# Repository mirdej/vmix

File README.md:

# ANYMIX 21

Multichannel modular analog PAL video mixer based on the SYNKIE project

The Anymix21 is a 12 channel analog video mixer based on the paradigm of classic audio mixing desks.

Each channel is a complete SYNKIE by itself, sort of. It can handle anything from DC to around 10Mhz, this means you can mix CV signals with audio with PAL composite video signals. Contrary to an audio mixer, inputs are DC coupled, with 0v being black and 0.7V white level. Negative levels are permitted but will be clipped at the final output stage.

Each channel has a built-in equaliser, switchable edges (bandpass), comparator and inverter effects, and a scale-bias module for adjusting brightness and contrast. The signal can then be routed to 3 main output mix busses and an auxiliary output.

Apart from the equalizer, the effects and mix levels are digitally controlled analog, so parameters can be recorded, automated, or controlled externally through MIDI. The desk can be synchronized to a MIDI clock (which is then quantized to the vertical blanking interval derived from the genlock input).

Still under construction, the first 6 channels have passed their endurance test running daily for weeks at the exhibiton “H.o.Me. – Heim für obsolete Medien” at Kunsthaus Langenthal.

### Documentation
- Architecture [Overview](./doc/architecture.md)
- Mixer Channel: [Flowchart and description](./doc/channel.md)
- Master Section: [Flowchart and description](./doc/master.md)

### Links
- [Build pictures and notes](https://www.anyma.ch/blogs/research/2021/04/07/building-the-anymix21/) on my blog
- [https://www.anyma.ch](https://www.anyma.ch)
- [https://www.synkie.net](https://www.synkie.net)
- [Videos on Vimeo](https://vimeo.com/showcase/8252873)
- [Synkie on Github](https://github.com/mirdej/synkie)

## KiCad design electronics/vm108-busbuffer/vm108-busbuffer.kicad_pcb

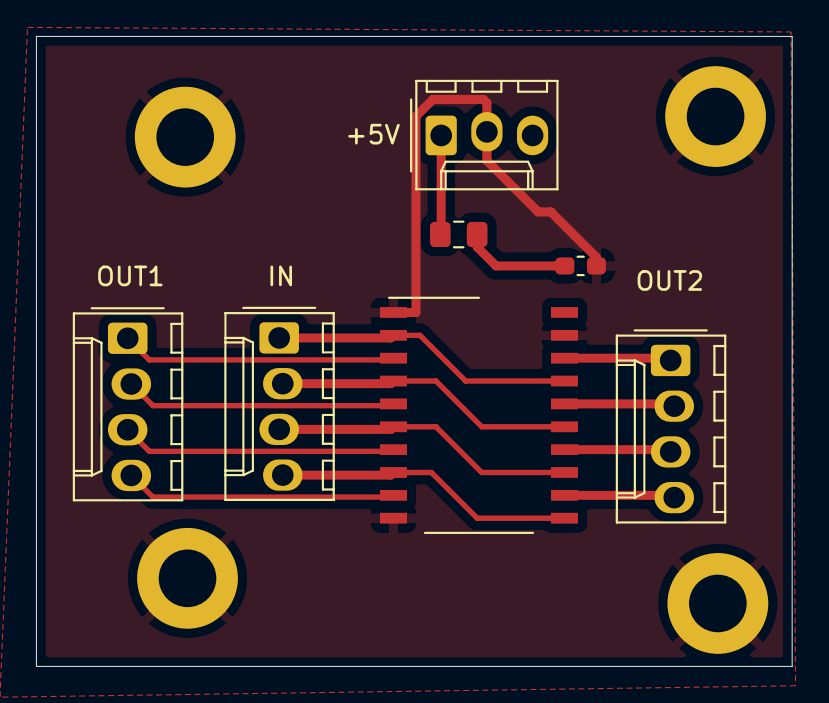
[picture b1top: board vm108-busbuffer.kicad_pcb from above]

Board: 2 copper layers, 42.0 x 35.0 mm, 11 parts (0 on the bottom side), 15 nets.

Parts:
C1: C; R_0603_1608Metric_Pad1.05x0.95mm_HandSolder
FB1: Ferrite_Bead; L_0805_2012Metric_Pad1.15x1.40mm_HandSolder
H1, H2, H3, H4: MountingHole_Pad; MountingHole_3.2mm_M3_DIN965_Pad
J1: Supply; Molex_KK-254_AE-6410-03A_1x03_P2.54mm_Vertical
J2, J3, J4: Sync-Bus; Molex_KK-254_AE-6410-04A_1x04_P2.54mm_Vertical
U1: 74HC244; SO-20_12.8x7.5mm_P1.27mm

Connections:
+5V: C1.1, FB1.2, U1.20 (VCC)
/supply+: FB1.1, J1.1
GND: C1.2, H1.1, H2.1, H3.1, H4.1, J1.2, U1.1 (1OE), U1.10 (GND), U1.19 (2OE)
unnamed: J2.1, U1.2 (1A0), U1.17 (2A0)
unnamed: J2.2, U1.4 (1A1), U1.15 (2A1)
unnamed: J2.3, U1.6 (1A2), U1.13 (2A2)
unnamed: J2.4, U1.8 (1A3), U1.11 (2A3)
unnamed: J3.1, U1.18 (1Y0)
unnamed: J3.2, U1.16 (1Y1)
unnamed: J3.3, U1.14 (1Y2)
unnamed: J3.4, U1.12 (1Y3)
unnamed: J4.1, U1.3 (2Y0)
unnamed: J4.2, U1.5 (2Y1)
unnamed: J4.3, U1.7 (2Y2)
unnamed: J4.4, U1.9 (2Y3)

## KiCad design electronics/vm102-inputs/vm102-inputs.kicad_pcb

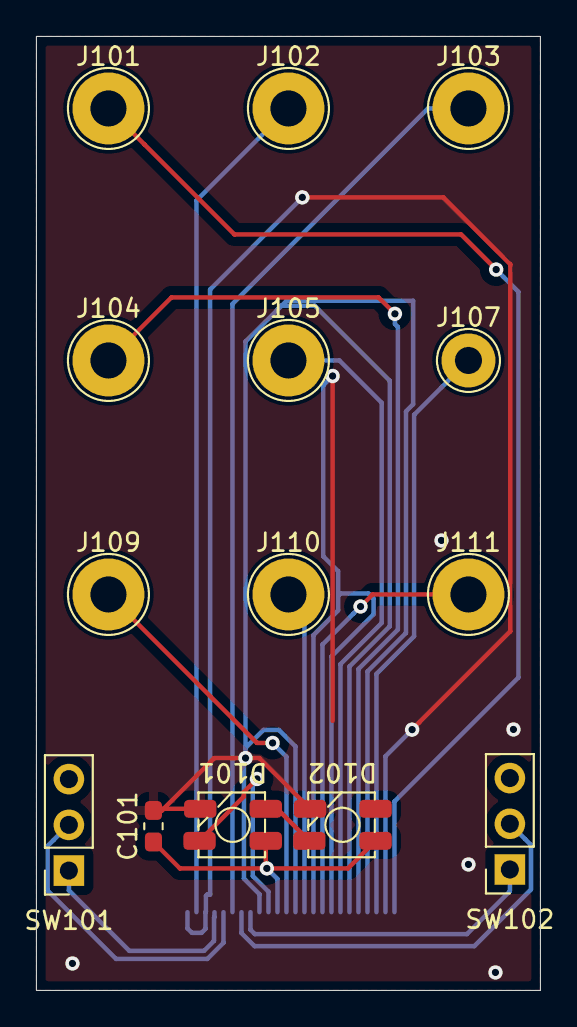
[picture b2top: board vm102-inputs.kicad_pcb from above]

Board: 2 copper layers, 28.0 x 53.0 mm, 15 parts (1 on the bottom side), 17 nets.

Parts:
C101: C; C_0603_1608Metric_Pad1.05x0.95mm_HandSolder
D101, D102: SK6812MINI; SK6812-MINI-HS
J101, J102, J103, J104, J105, J109, J110, J111: Conn; TestPoint_THTPad_D4.0mm_Drill2.0mm
J106: Conn_01x24_Shielded; Hirose_FH12-24S-0.5SH_1x24-1MP_P0.50mm_Horizontal
J107: Conn; TestPoint_THTPad_D3.0mm_Drill1.5mm
SW101, SW102: SW_SPDT; PinSocket_1x03_P2.54mm_Vertical

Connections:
/a: J106.12, J109.1
/aux: J105.1, J106.18
/b: J106.14, J110.1
/bias: J106.22, J107.1
/c: J106.16, J111.1
/compa-out: J102.1, J106.2
/hi_clip1: J106.8, SW102.1 (A)
/hi_clip2: J106.7, SW102.2 (B)
/lo_clip1: J106.4, SW101.1 (A)
/lo_clip2: J106.5, SW101.2 (B)
/output: J103.1, J106.6
/pixels: D101.3 (DIN), J106.10
/scale: J104.1, J106.20
/siff-in: J101.1, J106.24
GND: C101.2, D101.2 (VSS), D102.2 (VSS), J106.1, J106.3, J106.9, J106.13, J106.15, J106.17, J106.19, J106.21, J106.23
unnamed: D101.1 (DOUT), D102.3 (DIN)
VCC: C101.1, D101.4 (VDD), D102.4 (VDD), J106.11

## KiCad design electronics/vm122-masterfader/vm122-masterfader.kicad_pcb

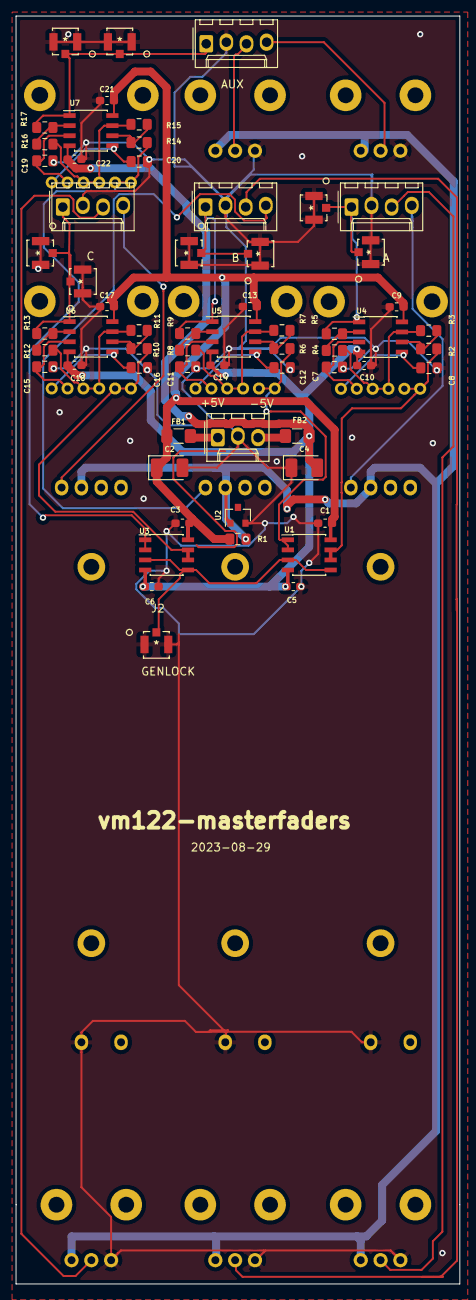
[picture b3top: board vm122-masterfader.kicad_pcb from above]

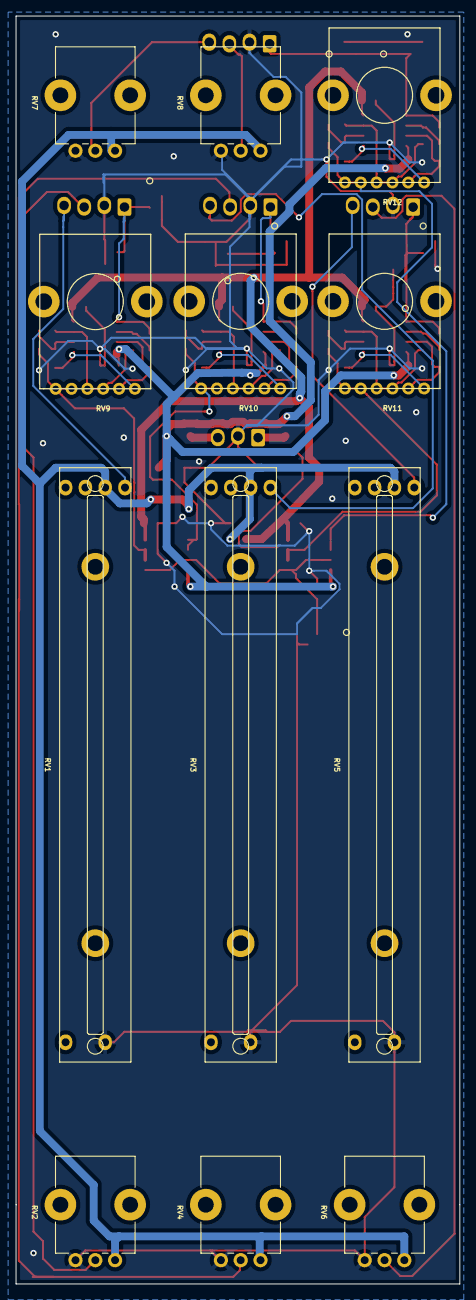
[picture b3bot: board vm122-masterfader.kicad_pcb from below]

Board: 2 copper layers, 56.0 x 160.0 mm, 74 parts (12 on the bottom side), 43 nets.

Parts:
C1, C3, C5, C6, C9, C10, C13, C14, C17, C18, C21, C22: 100n; C_0603_1608Metric_Pad1.05x0.95mm_HandSolder
C2, C4: CP; CP_EIA-3528-21_Kemet-B_Pad1.50x2.35mm_HandSolder
C7, C8, C11, C12, C15, C16, C19, C20: 10p; C_0805_2012Metric_Pad1.15x1.40mm_HandSolder
FB1, FB2: Ferrite_Bead; L_1206_3216Metric_Pad1.42x1.75mm_HandSolder
J1: Conn_01x03; Molex_KK-254_AE-6410-03A_1x03_P2.54mm_Vertical
J2, J7, J8, J9, J10, J11, J12, J13, J14: UMCC; TE_UMCC_2337019-1
J3: A; Molex_KK-254_AE-6410-04A_1x04_P2.54mm_Vertical
J4: B; Molex_KK-254_AE-6410-04A_1x04_P2.54mm_Vertical
J5: C; Molex_KK-254_AE-6410-04A_1x04_P2.54mm_Vertical
J6: D; Molex_KK-254_AE-6410-04A_1x04_P2.54mm_Vertical
R1: 560; R_0805_2012Metric_Pad1.15x1.40mm_HandSolder
R2, R3, R4, R5, R6, R7, R8, R9, R10, R11, R12, R13, R14, R15, R16, R17: 220; R_0805_2012Metric_Pad1.15x1.40mm_HandSolder
RV1, RV3, RV5: SCALE; Potentiometer_Alps_RS6011xP_Slide
RV2, RV4, RV6, RV8: BIAS; Potentiometer_Alps_RK09K_Single_Vertical
RV7: SCALE; Potentiometer_Alps_RK09K_Single_Vertical
RV9, RV10, RV11, RV12: R_POT_Dual; RK12L123
U1, U3, U4, U5, U6, U7: LMH6643; SOIC-8_3.9x4.9mm_P1.27mm
U2: ADR510; SOT-23

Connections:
+5V: C1.1, C2.1, C3.1, C9.2, C13.2, C17.2, C21.2, FB1.1, R1.1, U1.8 (V+), U3.8 (V+), U4.8 (V+), U5.8 (V+), U6.8 (V+), U7.8 (V+)
-5V: C4.2, C5.1, C6.1, C10.1, C14.1, C18.1, C22.1, FB2.1, U1.4 (V-), U3.4 (V-), U4.4 (V-), U5.4 (V-), U6.4 (V-), U7.4 (V-)
/Phase1/INPUT: R2.2, RV9.1, RV9.2, U1.6 (-), U1.7
/Phase1/OUTPUT: J3.1, J7.1, J8.1, R5.1, U4.1
/sheet5FF0F8E5/INPUT: R10.2, RV11.1, RV11.2, U3.6 (-), U3.7
/sheet5FF0F8E5/OUTPUT: J5.1, J11.1, J12.1, R13.1, U6.1
/sheet5FF0F40B/INPUT: R6.2, RV10.1, RV10.2, U1.1, U1.2 (-)
/sheet5FF0F40B/OUTPUT: J4.1, J9.1, J10.1, R9.1, U5.1
/sheet5FF0F904/INPUT: R14.2, RV12.1, RV12.2, U3.1, U3.2 (-)
/sheet5FF0F904/OUTPUT: J6.1, J13.1, J14.1, R17.1, U7.1
GND: C1.2, C2.2, C3.2, C4.1, C5.2, C6.2, C7.2, C8.2, C9.1, C10.2, C11.2, C12.2, C13.1, C14.2, C15.2, C16.2, C17.1, C18.2, C19.2, C20.2, C21.1, C22.2, J1.2, J2.2, J2.3, J3.2, J4.2, J5.2, J6.2, J7.2, J7.3, J8.2, J8.3, J9.2, J9.3, J10.2, J10.3, J11.2, J11.3, J12.2, J12.3, J13.2, J13.3, J14.2, J14.3, RV1.3, RV2.3, RV3.3, RV4.3, RV5.3, RV6.3, RV7.3, RV8.3, U2.2 (V-)
unnamed: C7.1, RV9.6, U4.3 (+)
unnamed: C8.1, RV9.3, U4.5 (+)
unnamed: C11.1, RV10.6, U5.3 (+)
unnamed: C12.1, RV10.3, U5.5 (+)
unnamed: C15.1, RV11.6, U6.3 (+)
unnamed: C16.1, RV11.3, U6.5 (+)
unnamed: C19.1, RV12.6, U7.3 (+)
unnamed: C20.1, RV12.3, U7.5 (+)
unnamed: FB1.2, J1.1
unnamed: FB2.2, J1.3
unnamed: J3.3, RV2.2
unnamed: J3.4, RV1.2
unnamed: J4.3, RV4.2
unnamed: J4.4, RV3.2
unnamed: J5.3, RV6.2
unnamed: J5.4, RV5.2
unnamed: J6.3, RV8.2
unnamed: J6.4, RV7.2
unnamed: R2.1, R3.2, U4.6 (-)
unnamed: R3.1, R4.2, RV9.4, RV9.5, U4.7
unnamed: R4.1, R5.2, U4.2 (-)
unnamed: R6.1, R7.2, U5.6 (-)
unnamed: R7.1, R8.2, RV10.4, RV10.5, U5.7
unnamed: R8.1, R9.2, U5.2 (-)
unnamed: R10.1, R11.2, U6.6 (-)
unnamed: R11.1, R12.2, RV11.4, RV11.5, U6.7
unnamed: R12.1, R13.2, U6.2 (-)
unnamed: R14.1, R15.2, U7.6 (-)
unnamed: R15.1, R16.2, RV12.4, RV12.5, U7.7
unnamed: R16.1, R17.2, U7.2 (-)
unnamed: J2.1, U1.3 (+), U1.5 (+), U3.3 (+), U3.5 (+)
VCCQ: R1.2, RV1.1, RV2.1, RV3.1, RV4.1, RV5.1, RV6.1, RV7.1, RV8.1, U2.1 (V+)

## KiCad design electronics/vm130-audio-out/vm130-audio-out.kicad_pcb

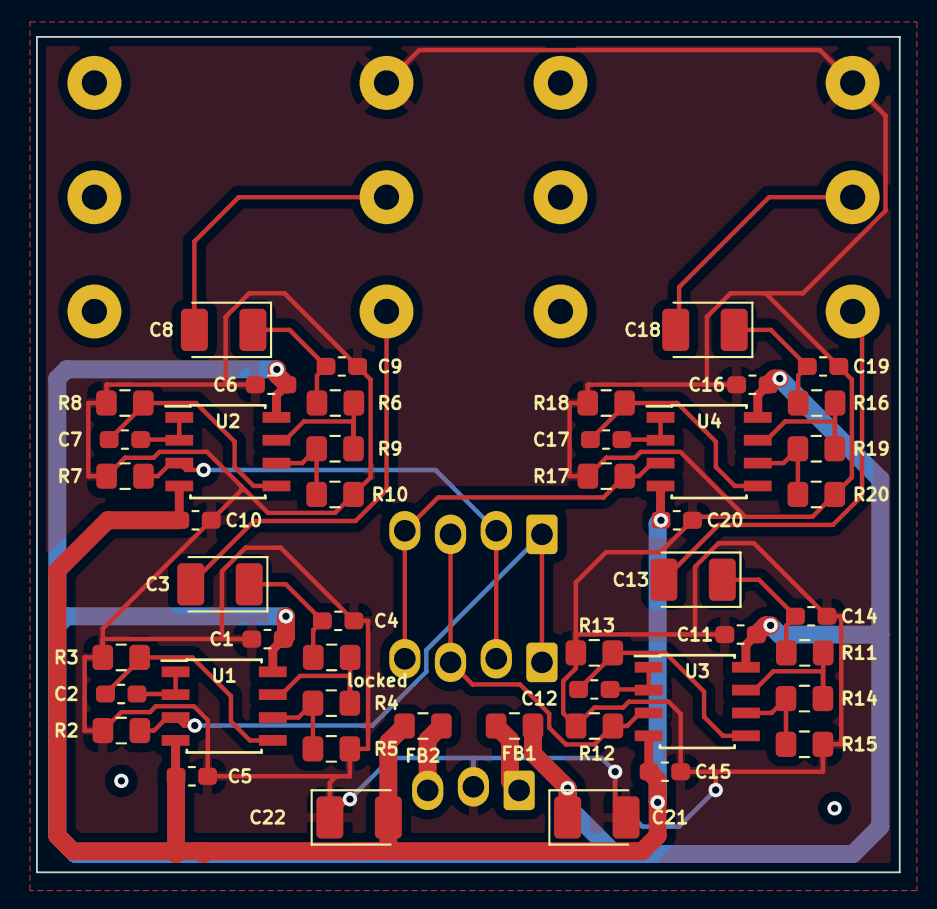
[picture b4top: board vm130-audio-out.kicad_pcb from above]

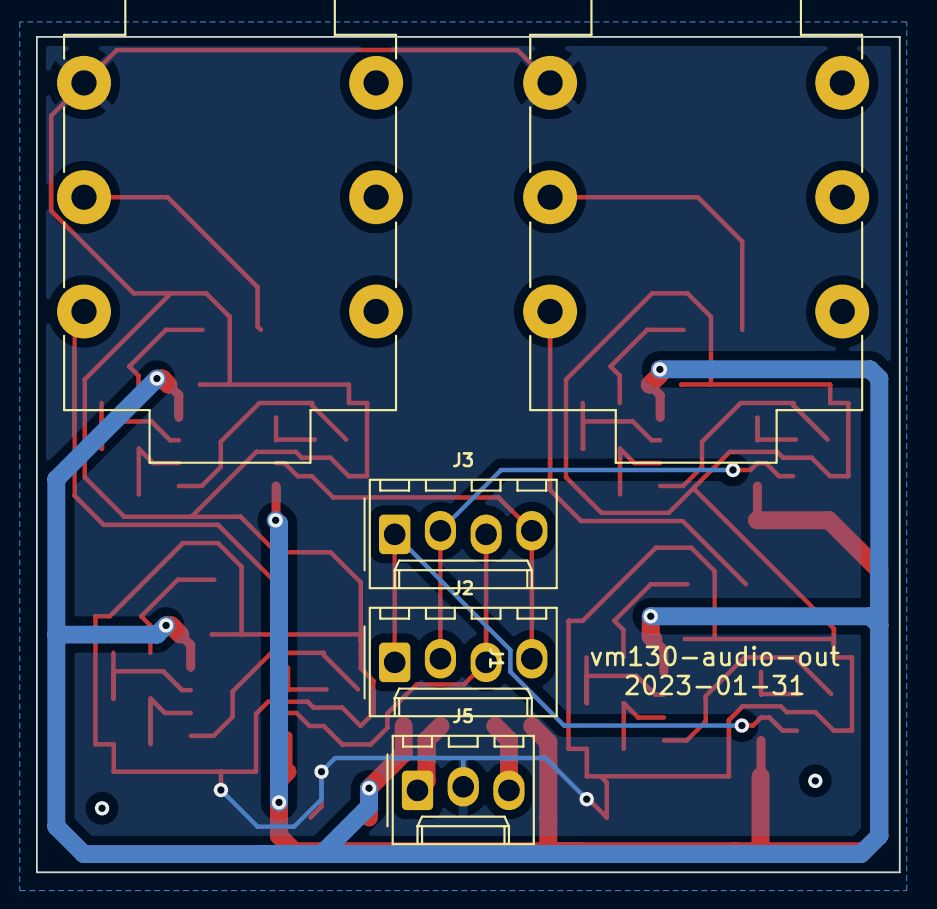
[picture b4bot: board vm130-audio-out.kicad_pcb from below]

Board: 2 copper layers, 47.9 x 46.4 mm, 53 parts (5 on the bottom side), 33 nets.

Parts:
C1, C4, C5, C6, C9, C10, C11, C14, C15, C16, C19, C20: 100n; C_0603_1608Metric_Pad1.05x0.95mm_HandSolder
C2, C7, C12, C17: 1u; C_0603_1608Metric_Pad1.05x0.95mm_HandSolder
C3, C8, C13, C18: 100u; CP_EIA-3528-21_Kemet-B_Pad1.50x2.35mm_HandSolder
C21, C22: CP; CP_EIA-3528-21_Kemet-B_Pad1.50x2.35mm_HandSolder
FB1, FB2: FerriteBead; L_0805_2012Metric_Pad1.15x1.40mm_HandSolder
J1, J4: AudioJack3_Switch; Jack_6.35mm_Neutrik_NMJ6HCD3_Horizontal
J2, J3: Conn_01x04; Molex_KK-254_AE-6410-04A_1x04_P2.54mm_Vertical
J5: Conn_01x03; Molex_KK-254_AE-6410-03A_1x03_P2.54mm_Vertical
R2, R7, R12, R17: 47k; C_0805_2012Metric_Pad1.15x1.40mm_HandSolder
R3, R8, R13, R18: 10k; C_0805_2012Metric_Pad1.15x1.40mm_HandSolder
R4, R5, R9, R10, R14, R15, R19, R20: 500; C_0805_2012Metric_Pad1.15x1.40mm_HandSolder
R6, R11, R16: 75; C_0805_2012Metric_Pad1.15x1.40mm_HandSolder
U1, U2, U3, U4: Opamp_Dual_Generic; SOIC-8_3.9x4.9mm_P1.27mm
locked: 75; C_0805_2012Metric_Pad1.15x1.40mm_HandSolder

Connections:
+5V: C1.2, C6.2, C11.2, C16.2, C21.1, FB1.2, U1.8 (V+), U2.8 (V+), U3.8 (V+), U4.8 (V+)
-5V: C5.2, C10.2, C15.2, C20.2, C22.2, FB2.2, U1.4 (V-), U2.4 (V-), U3.4 (V-), U4.4 (V-)
/channel1/out: C8.2, J1.R
/channel2/out: C13.2, J4.T
/channel3/out: C18.2, J4.R
/channel/out: C3.2, J1.T
/in-a: J2.1, J3.1, R2.1, U1.3 (+)
/in-b: J2.2, J3.2, R7.1, U2.3 (+)
/in-c: J2.3, J3.3, R12.1, U3.3 (+)
/in-d: J2.4, J3.4, R17.1, U4.3 (+)
GND: C1.1, C4.1, C5.1, C6.1, C9.1, C10.1, C11.1, C14.1, C15.1, C16.1, C19.1, C20.1, C21.2, C22.1, J1.S, J4.S, J5.2, R2.2, R3.2, R5.2, R7.2, R8.2, R10.2, R12.2, R13.2, R15.2, R17.2, R18.2, R20.2
unnamed: C2.1, U1.1, U1.2 (-)
unnamed: C2.2, R3.1, U1.5 (+)
unnamed: C3.1, C4.2, locked.2
unnamed: C7.1, U2.1, U2.2 (-)
unnamed: C7.2, R8.1, U2.5 (+)
unnamed: C8.1, C9.2, R6.2
unnamed: C12.1, U3.1, U3.2 (-)
unnamed: C12.2, R13.1, U3.5 (+)
unnamed: C13.1, C14.2, R11.2
unnamed: C17.1, U4.1, U4.2 (-)
unnamed: C17.2, R18.1, U4.5 (+)
unnamed: C18.1, C19.2, R16.2
unnamed: FB1.1, J5.1
unnamed: FB2.1, J5.3
unnamed: R4.2, U1.7, locked.1
unnamed: R4.1, R5.1, U1.6 (-)
unnamed: R6.1, R9.2, U2.7
unnamed: R9.1, R10.1, U2.6 (-)
unnamed: R11.1, R14.2, U3.7
unnamed: R14.1, R15.1, U3.6 (-)
unnamed: R16.1, R19.2, U4.7
unnamed: R19.1, R20.1, U4.6 (-)

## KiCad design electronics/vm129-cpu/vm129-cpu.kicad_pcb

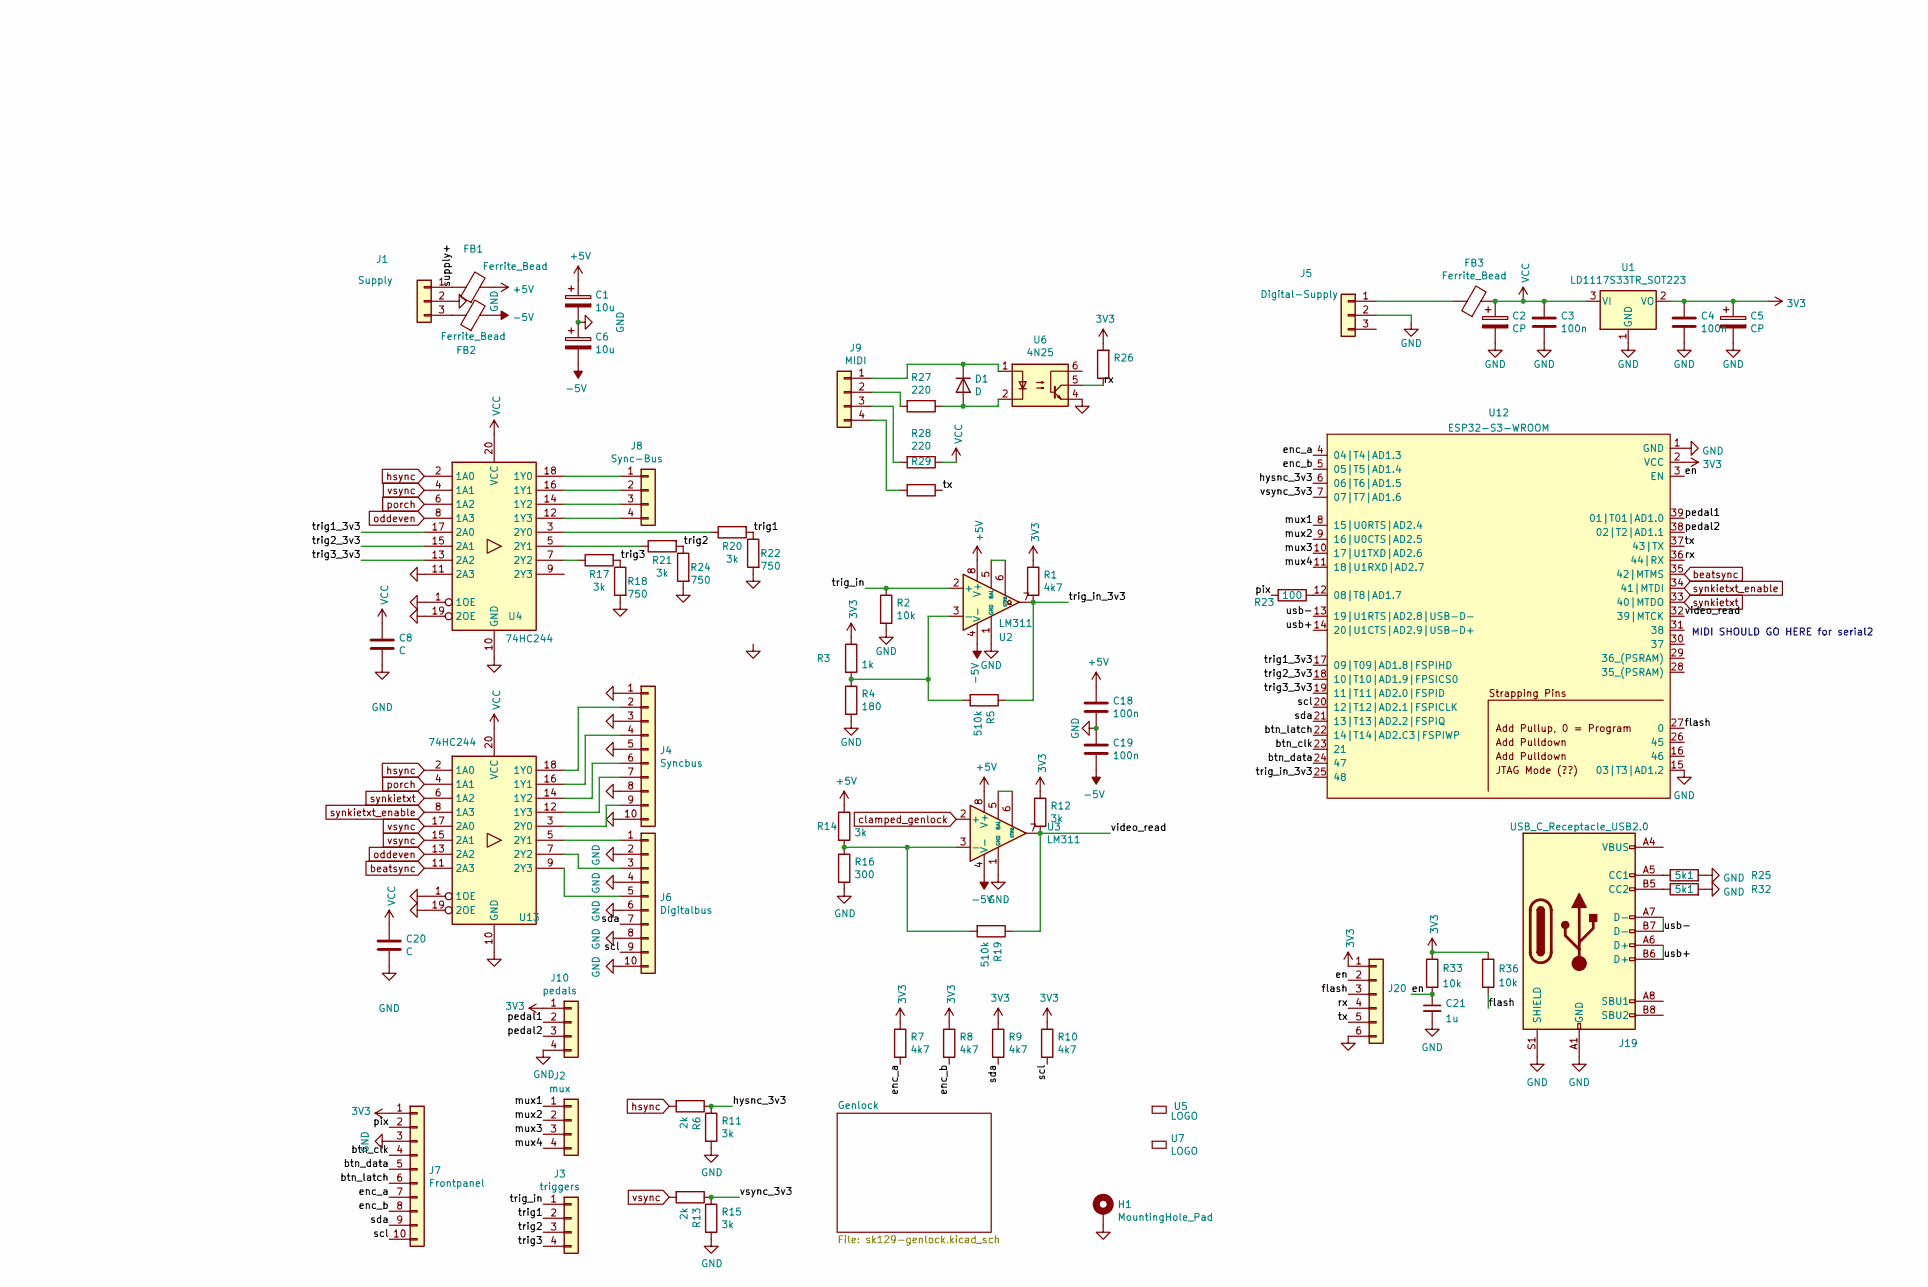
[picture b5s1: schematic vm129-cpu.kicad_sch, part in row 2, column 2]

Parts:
C1, C6: 10u; CP_EIA-3528-21_Kemet-B_Pad1.50x2.35mm_HandSolder
C2, C5: CP; CP_EIA-3528-21_Kemet-B_Pad1.50x2.35mm_HandSolder
C3, C4, C18, C19: 100n; C_0603_1608Metric_Pad1.05x0.95mm_HandSolder
C8, C20: C; R_0603_1608Metric_Pad1.05x0.95mm_HandSolder
C21: 1u; C_0603_1608Metric_Pad1.05x0.95mm_HandSolder
D1: D; D_MiniMELF
FB1, FB2, FB3: Ferrite_Bead; L_0805_2012Metric_Pad1.15x1.40mm_HandSolder
H1: MountingHole_Pad; MountingHole_2.7mm_M2.5_ISO7380_Pad
J1: Supply; Molex_KK-254_AE-6410-03A_1x03_P2.54mm_Vertical
J2: mux; Molex_KK-254_AE-6410-04A_1x04_P2.54mm_Vertical
J3: triggers; Molex_KK-254_AE-6410-04A_1x04_P2.54mm_Vertical
J4: Syncbus; IDC-Header_2x05_P2.54mm_Vertical
J5: Digital-Supply; Molex_KK-254_AE-6410-03A_1x03_P2.54mm_Vertical
J6: Digitalbus; IDC-Header_2x05_P2.54mm_Vertical
J7: Frontpanel; IDC-Header_2x05_P2.54mm_Vertical
J8: Sync-Bus; Molex_KK-254_AE-6410-04A_1x04_P2.54mm_Vertical
J9: MIDI; Molex_KK-254_AE-6410-04A_1x04_P2.54mm_Vertical
J10: pedals; Molex_KK-254_AE-6410-04A_1x04_P2.54mm_Vertical
J19: USB_C_Receptacle_USB2.0; JAE_USB-C_SJ122205
J20: Conn_01x06; AnymaPOGO-ISP
R1, R7, R8, R9, R10: 4k7; R_0805_2012Metric_Pad1.15x1.40mm_HandSolder
R2, R33, R36: 10k; R_0805_2012Metric_Pad1.15x1.40mm_HandSolder
R3: 1k; R_0805_2012Metric_Pad1.15x1.40mm_HandSolder
R4: 180; R_0805_2012Metric_Pad1.15x1.40mm_HandSolder
R5, R19: 510k; R_0805_2012Metric_Pad1.15x1.40mm_HandSolder
R6, R13: 2k; R_0805_2012Metric_Pad1.15x1.40mm_HandSolder
R11, R12, R14, R15, R17, R20, R21: 3k; R_0805_2012Metric_Pad1.15x1.40mm_HandSolder
R16: 300; R_0805_2012Metric_Pad1.15x1.40mm_HandSolder
R18, R22, R24: 750; R_0805_2012Metric_Pad1.15x1.40mm_HandSolder
R23: 100; R_0805_2012Metric_Pad1.15x1.40mm_HandSolder
R25, R32: 5k1; R_0805_2012Metric_Pad1.15x1.40mm_HandSolder
R26, R29: R_0805_2012Metric_Pad1.15x1.40mm_HandSolder
R27, R28: 220; R_0805_2012Metric_Pad1.15x1.40mm_HandSolder
U1: LD1117S33TR_SOT223; SOT-223-3_TabPin2
U2, U3: LM311; SOIC-8_3.9x4.9mm_P1.27mm
U4, U13: 74HC244; SO-20_12.8x7.5mm_P1.27mm
U5: LOGO; logo_anyma
U6: 4N25; DIP-6_W8.89mm_SMDSocket_LongPads
U7: LOGO; OSHW-Logo2_7.3x6mm_SilkScreen
U12: ESP32-S3-WROOM

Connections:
3V3: C4.1, C5.1, J7.1, J10.1, J20.1, R1.1, R3.1, R7.1, R8.1, R9.1, R10.1, R12.1, R26.2, R33.1, R36.1, U1.2 (VO), U12.2 (VCC)
+5V: C1.1, C18.1, FB1.2, R14.1, U2.8 (V+), U3.8 (V+); also elsewhere on the board
-5V: C6.2, C19.2, FB2.2, U2.4 (V-), U3.4 (V-); also elsewhere on the board
/btn_clk: J7.4, U12.23 (21)
/btn_data: J7.5, U12.24 (47)
/btn_latch: J7.6, U12.22 (14|T14|AD2.C3|FSPIWP)
/en: C21.1, J20.2, R33.2, U12.3 (EN)
/enc_a: J7.7, R7.2, U12.4 (04|T4|AD1.3)
/enc_b: J7.8, R8.2, U12.5 (05|T5|AD1.4)
/flash: J20.3, R36.2, U12.27 (0)
/hysnc_3v3: R6.1, R11.1, U12.6 (06|T6|AD1.5)
/mux1: J2.1, U12.8 (15|U0RTS|AD2.4)
/mux2: J2.2, U12.9 (16|U0CTS|AD2.5)
/mux3: J2.3, U12.10 (17|U1TXD|AD2.6)
/mux4: J2.4, U12.11 (18|U1RXD|AD2.7)
/pedal1: J10.2, U12.39 (01|T01|AD1.0)
/pedal2: J10.3, U12.38 (02|T2|AD1.1)
/pix: J7.2, R23.2
/rx: J20.4, R26.1, U6.5, U12.36 (44|RX)
/scl: J6.9, J7.10, R10.2, U12.20 (12|T12|AD2.1|FSPICLK)
/sda: J6.7, J7.9, R9.2, U12.21 (13|T13|AD2.2|FSPIQ)
/supply+: FB1.1, J1.1
/trig1: J3.2, R20.2, R22.1
/trig1_3v3: U4.17 (2A0), U12.17 (09|T09|AD1.8|FSPIHD)
/trig2: J3.3, R21.2, R24.1
/trig2_3v3: U4.15 (2A1), U12.18 (10|T10|AD1.9|FPSICS0)
/trig3: J3.4, R17.2, R18.1
/trig3_3v3: U4.13 (2A2), U12.19 (11|T11|AD2.0|FSPID)
/trig_in: J3.1, R2.1, U2.2 (+)
/trig_in_3v3: R1.2, R5.1, U2.7, U12.25 (48)
/tx: J20.5, R29.1, U12.37 (43|TX)
/usb+: J19.A6 (D+), J19.B6 (D+), U12.14 (20|U1CTS|AD2.9|USB-D+)
/usb-: J19.A7 (D-), J19.B7 (D-), U12.13 (19|U1RTS|AD2.8|USB-D-)
/video_read: R12.2, R19.1, U3.7, U12.32 (39|MTCK)
/vsync_3v3: R13.1, R15.1, U12.7 (07|T7|AD1.6)
GND: C1.2, C2.2, C3.2, C4.2, C5.2, C6.1, C8.2, C18.2, C19.1, C20.2, C21.2, H1.1, J1.2, J4.1, J4.3, J4.5, J4.8, J4.10, J5.2, J6.2, J6.4, J6.6, J6.8, J6.10, J7.3, J10.4, J19.A1 (GND), J19.A12 (GND), J19.B1 (GND), J19.B12 (GND), J19.S1 (SHIELD), J20.6, R2.2, R4.2, R11.2, R15.2, R16.2, R18.2, R22.2, R24.2, R25.2, R32.2, U1.1 (GND), U2.1 (GND), U3.1 (GND), U4.1 (1OE), U4.10 (GND), U4.11 (2A3), U4.19 (2OE), U6.4, U12.1 (GND), U12.15 (03|T3|AD1.2), U12.40 (GND), U12.41 (GND), U13.1 (1OE), U13.10 (GND), U13.19 (2OE); also elsewhere on the board
unnamed: D1.1 (K), J9.1, U6.1
unnamed: D1.2 (A), R27.1, U6.2
unnamed: FB2.1, J1.3
unnamed: FB3.1, J5.1
unnamed: J4.2, U13.18 (1Y0)
unnamed: J4.4, U13.16 (1Y1)
unnamed: J4.6, U13.14 (1Y2)
unnamed: J4.7, U13.12 (1Y3)
unnamed: J4.9, U13.3 (2Y0)
unnamed: J6.1, U13.5 (2Y1)
unnamed: J6.3, U13.7 (2Y2)
unnamed: J6.5, U13.9 (2Y3)
unnamed: J8.1, U4.18 (1Y0)
unnamed: J8.2, U4.16 (1Y1)
unnamed: J8.3, U4.14 (1Y2)
unnamed: J8.4, U4.12 (1Y3)
unnamed: J19.A4 (VBUS), J19.A9 (VBUS), J19.B4 (VBUS), J19.B9 (VBUS)
unnamed: J19.A5 (CC1), R25.1
unnamed: J19.B5 (CC2), R32.1
unnamed: R3.2, R4.1, R5.2, U2.3 (-)
unnamed: R14.2, R16.1, R19.2, U3.3 (-)
unnamed: R17.1, U4.7 (2Y2)
unnamed: R20.1, U4.3 (2Y0)
unnamed: R21.1, U4.5 (2Y1)
unnamed: R23.1, U12.12 (08|T8|AD1.7)
unnamed: J9.2, R27.2
unnamed: J9.3, R28.2
unnamed: J9.4, R29.2
unnamed: U2.5 (BAL), U2.6 (STRB)
unnamed: U3.5 (BAL), U3.6 (STRB)
VCC: C2.1, C3.1, C8.1, C20.1, FB3.2, R28.1, U1.3 (VI), U4.20 (VCC), U13.20 (VCC)
beatsync: U12.35 (42|MTMS), U13.11 (2A3)
clamped_genlock: U3.2 (+); also elsewhere on the board
hsync: R6.2, U4.2 (1A0), U13.2 (1A0); also elsewhere on the board
oddeven: U4.8 (1A3), U13.13 (2A2); also elsewhere on the board
porch: U4.6 (1A2), U13.4 (1A1); also elsewhere on the board
synkietxt: U12.33 (40|MTDO), U13.6 (1A2)
synkietxt_enable: U12.34 (41|MTDI), U13.8 (1A3)
vsync: R13.2, U4.4 (1A1), U13.15 (2A1), U13.17 (2A0); also elsewhere on the board

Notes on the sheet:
MIDI SHOULD GO HERE for serial2

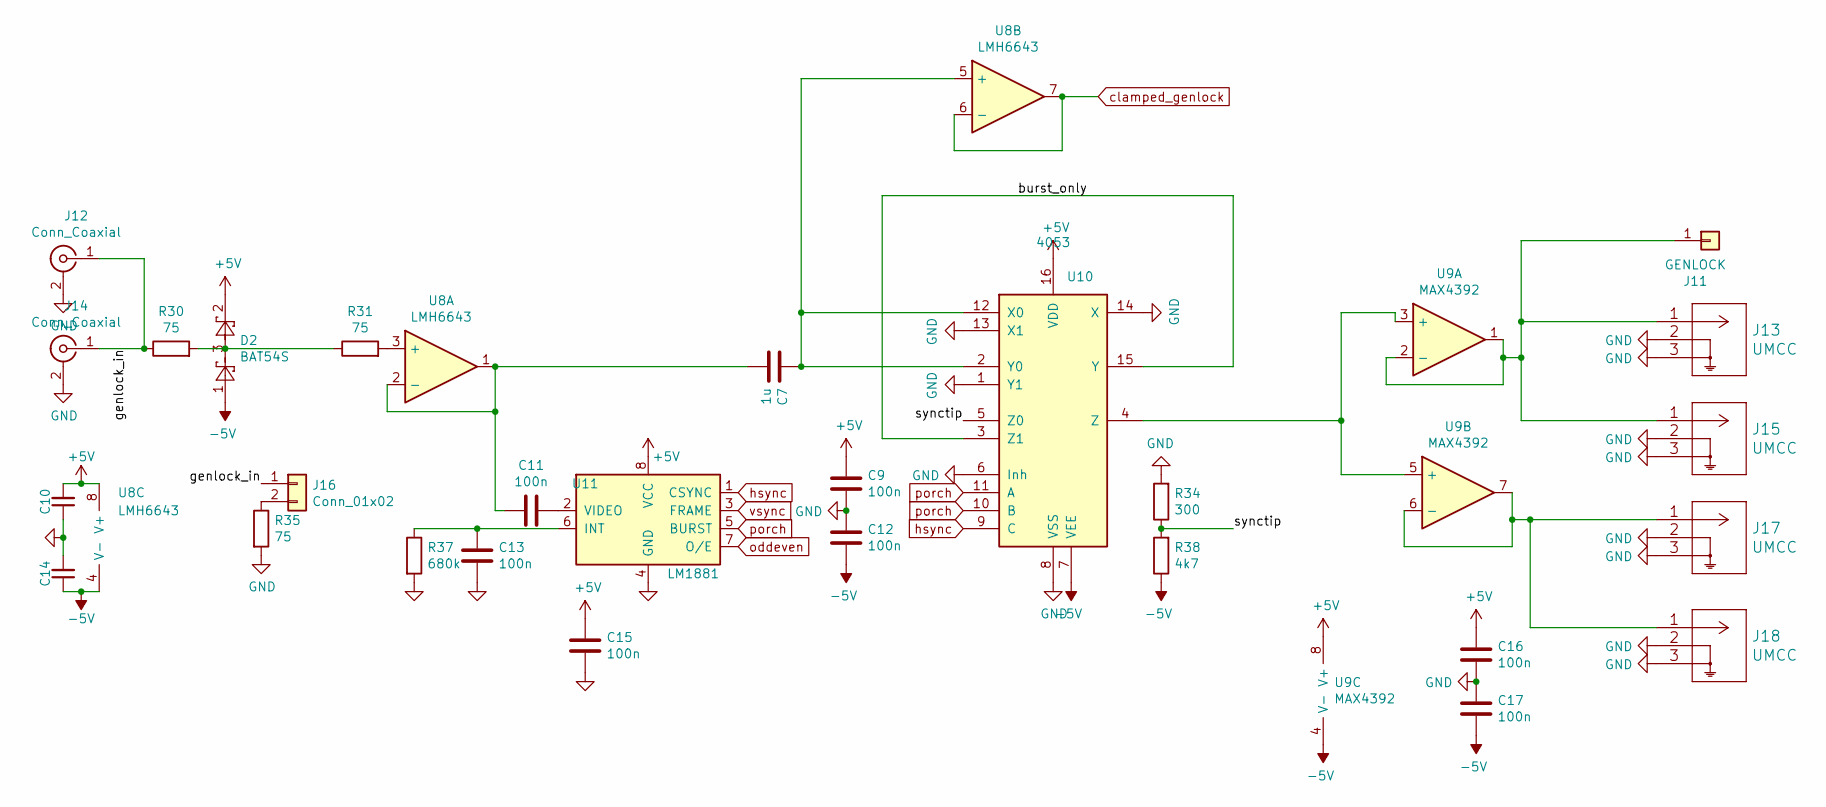
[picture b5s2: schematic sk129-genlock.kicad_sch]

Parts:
C7: 1u; C_1206_3216Metric_Pad1.42x1.75mm_HandSolder
C9, C10, C11, C12, C13, C14, C15, C16, C17: 100n; C_0603_1608Metric_Pad1.05x0.95mm_HandSolder
D2: BAT54S; SOT-23
J11: GENLOCK; Solderpad_1mm
J12, J14: Conn_Coaxial; BNC_MOLEX_0731000080_Horizontal
J13, J15, J17, J18: UMCC; TE_UMCC_2337019-1
J16: Conn_01x02; PinHeader_1x02_P2.54mm_Vertical
R30, R31, R35: 75; R_0805_2012Metric_Pad1.15x1.40mm_HandSolder
R34: 300; R_1206_3216Metric_Pad1.42x1.75mm_HandSolder
R37: 680k; R_0805_2012Metric_Pad1.15x1.40mm_HandSolder
R38: 4k7; R_1206_3216Metric_Pad1.42x1.75mm_HandSolder
U8: LMH6643; SOIC-8_3.9x4.9mm_P1.27mm
U9: MAX4392; SOIC-8_3.9x4.9mm_P1.27mm
U10: 4053; SOIC-16_3.9x9.9mm_P1.27mm
U11: LM1881; SOIC-8_3.9x4.9mm_P1.27mm

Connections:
+5V: C9.1, C10.2, C15.1, C16.1, D2.2, U8.8 (V+), U9.8 (V+), U10.16 (VDD), U11.8 (VCC); also elsewhere on the board
-5V: C12.2, C14.1, C17.2, D2.1, R38.1, U8.4 (V-), U9.4 (V-), U10.7 (VEE); also elsewhere on the board
/Genlock/burst_only: U10.3 (Z1), U10.15 (Y)
/Genlock/genlock_in: J12.1 (In), J14.1 (In), J16.1, R30.1
/Genlock/synctip: R34.1, R38.2, U10.5 (Z0)
GND: C9.2, C10.1, C12.1, C13.2, C14.2, C15.2, C16.2, C17.1, J12.2 (Ext), J13.2, J13.3, J14.2 (Ext), J15.2, J15.3, J17.2, J17.3, J18.2, J18.3, R34.2, R35.2, R37.2, U10.1 (Y1), U10.6 (Inh), U10.8 (VSS), U10.13 (X1), U10.14 (X), U11.4 (GND); also elsewhere on the board
unnamed: C7.1, U8.5 (+), U10.2 (Y0), U10.12 (X0)
unnamed: C11.1, U11.2 (VIDEO)
unnamed: C7.2, C11.2, U8.1, U8.2 (-)
unnamed: C13.1, R37.1, U11.6 (INT)
unnamed: D2.3, R30.2, R31.1
unnamed: J16.2, R35.1
unnamed: J17.1, J18.1, U9.6 (-), U9.7
unnamed: R31.2, U8.3 (+)
unnamed: J11.1, J13.1, J15.1, U9.1, U9.2 (-)
unnamed: U9.3 (+), U9.5 (+), U10.4 (Z)
clamped_genlock: U8.6 (-), U8.7; also elsewhere on the board
hsync: U10.9 (C), U11.1 (CSYNC); also elsewhere on the board
oddeven: U11.7 (O/E); also elsewhere on the board
porch: U10.10 (B), U10.11 (A), U11.5 (BURST); also elsewhere on the board
vsync: U11.3 (FRAME); also elsewhere on the board

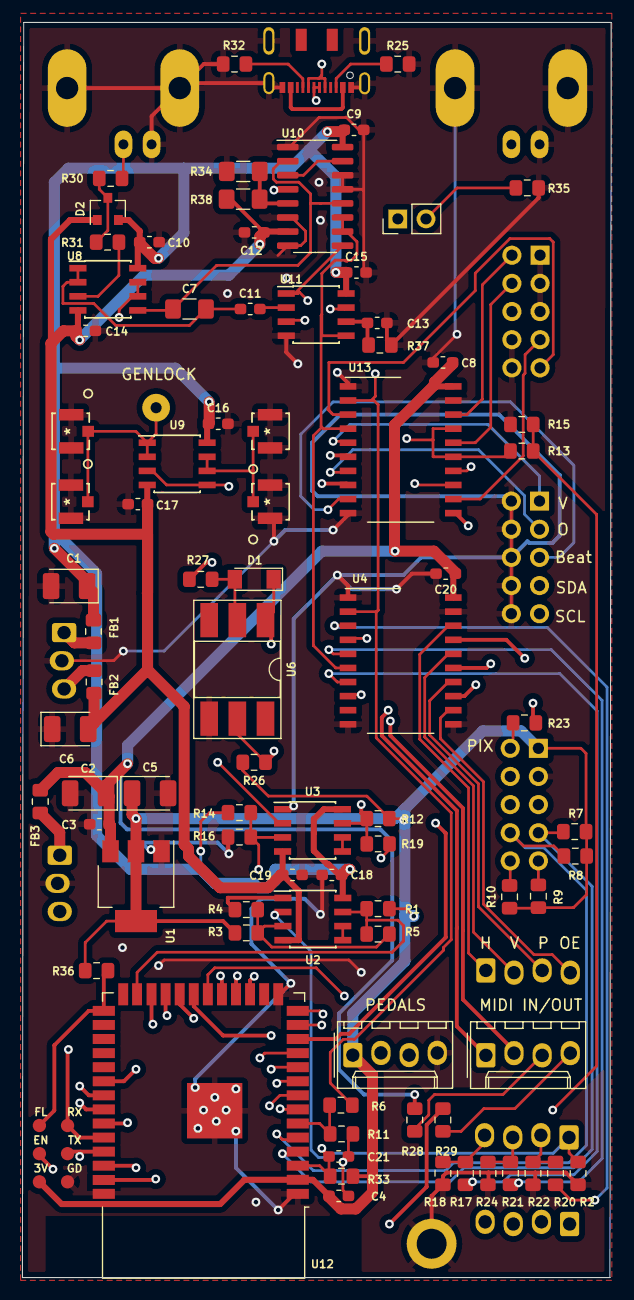
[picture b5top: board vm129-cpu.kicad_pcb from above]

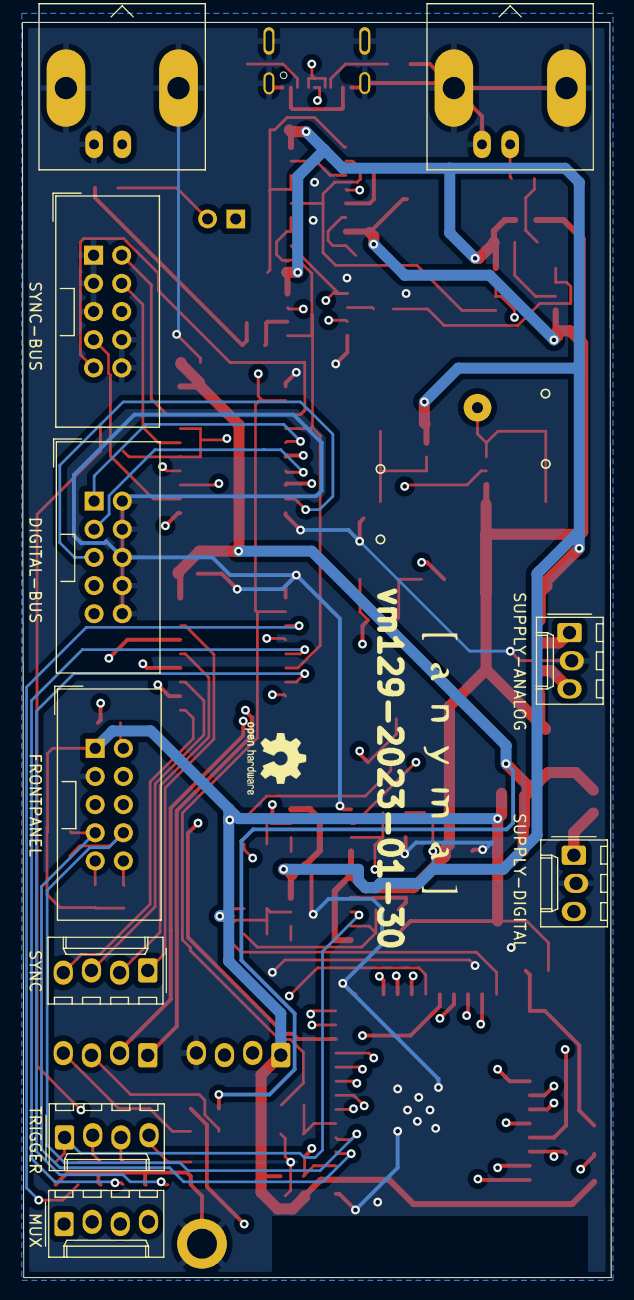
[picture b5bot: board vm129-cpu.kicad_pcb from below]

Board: 4 copper layers, 53.1 x 113.2 mm, 98 parts (12 on the bottom side), 88 nets.

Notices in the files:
parts and their libraries:
Copyright 2016 Accelerated Designs. All rights reserved.
